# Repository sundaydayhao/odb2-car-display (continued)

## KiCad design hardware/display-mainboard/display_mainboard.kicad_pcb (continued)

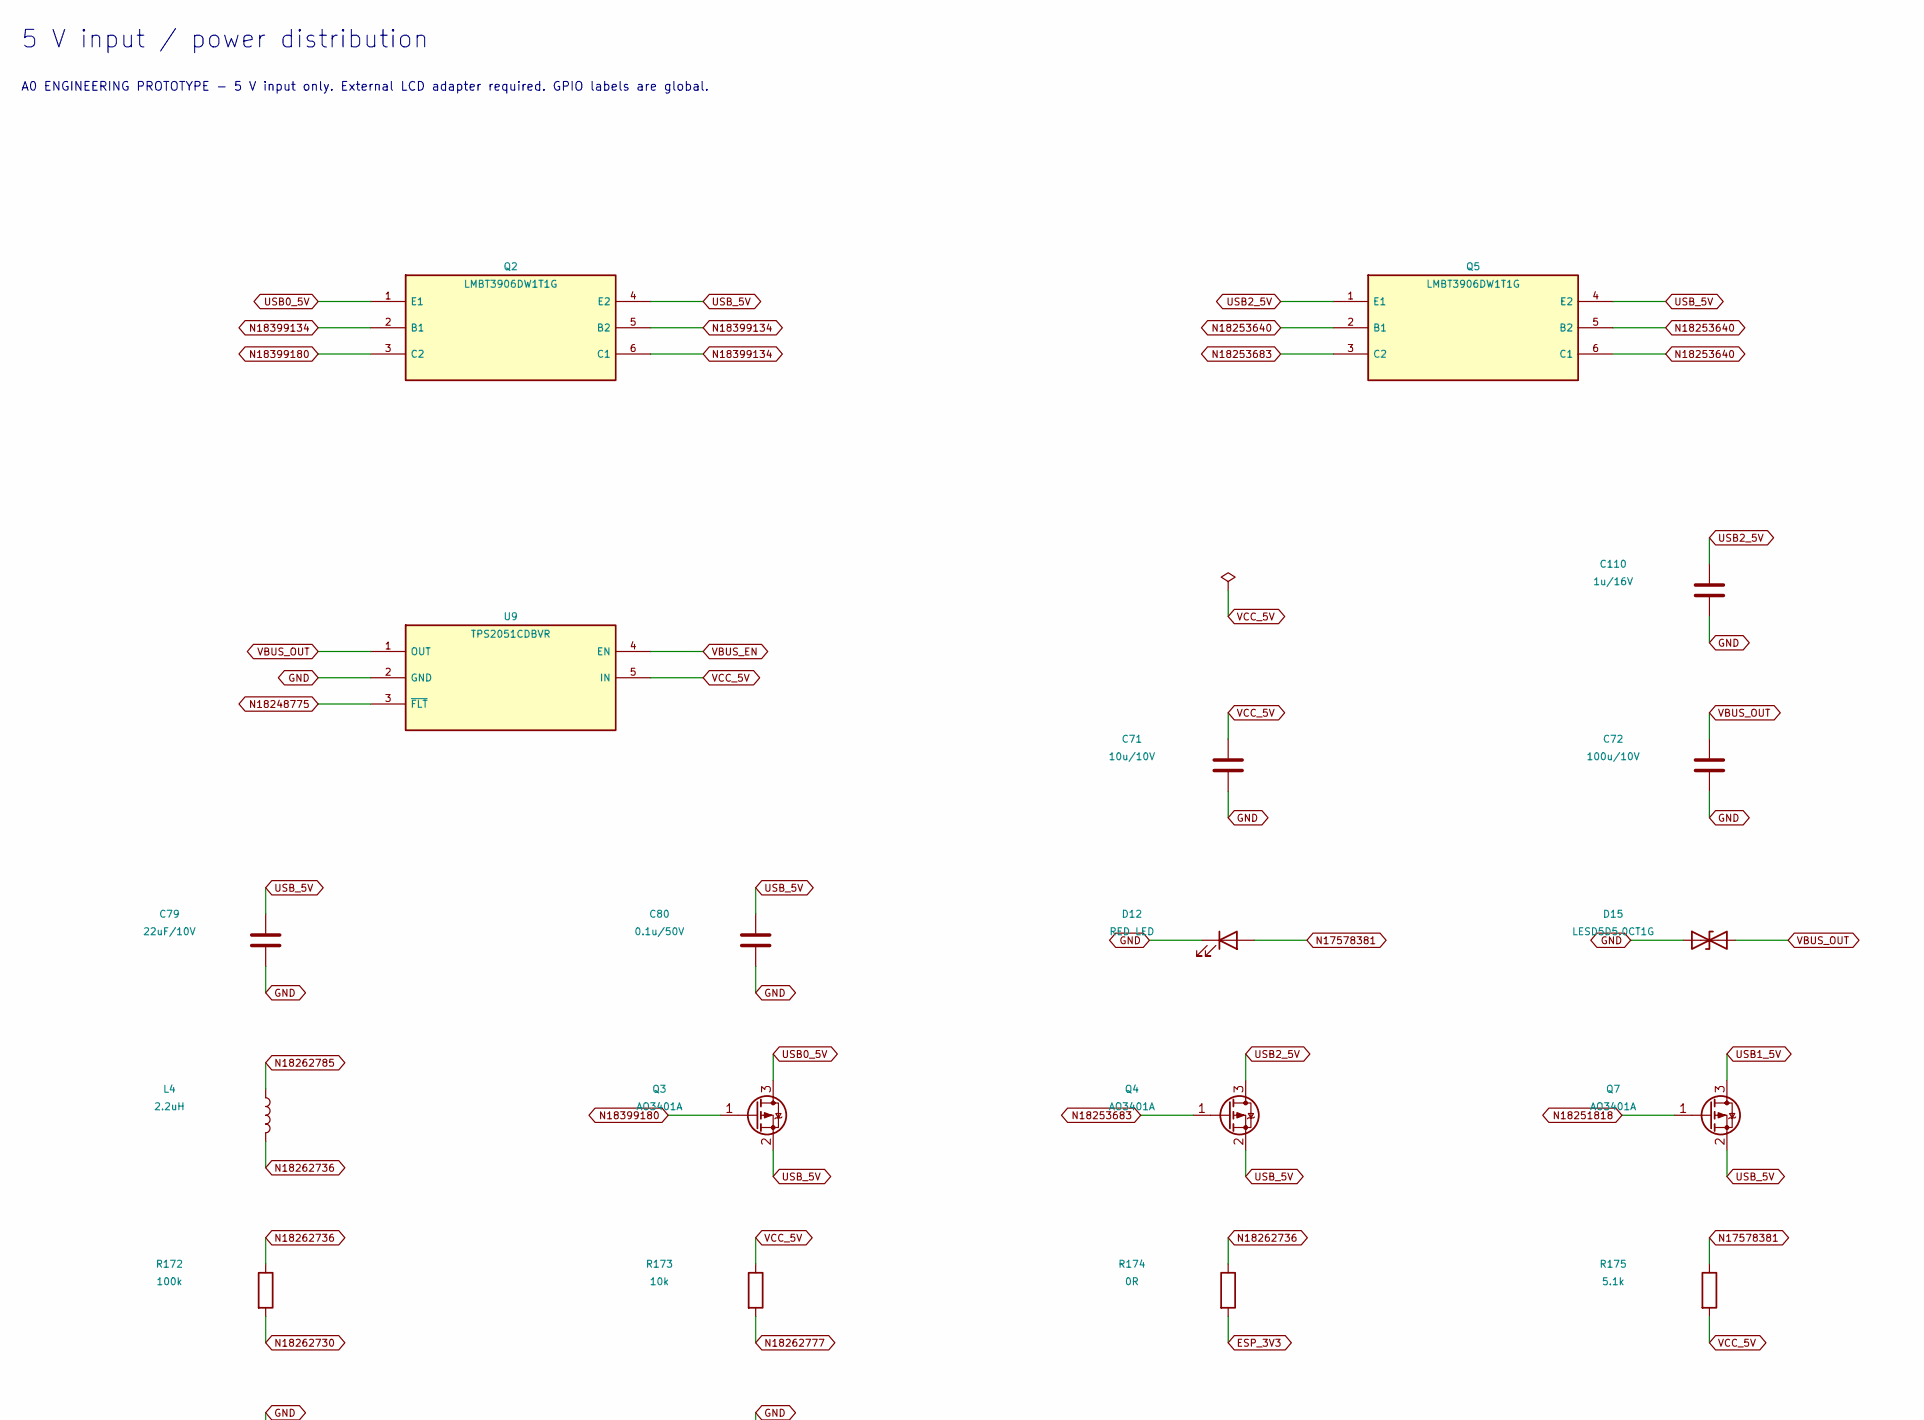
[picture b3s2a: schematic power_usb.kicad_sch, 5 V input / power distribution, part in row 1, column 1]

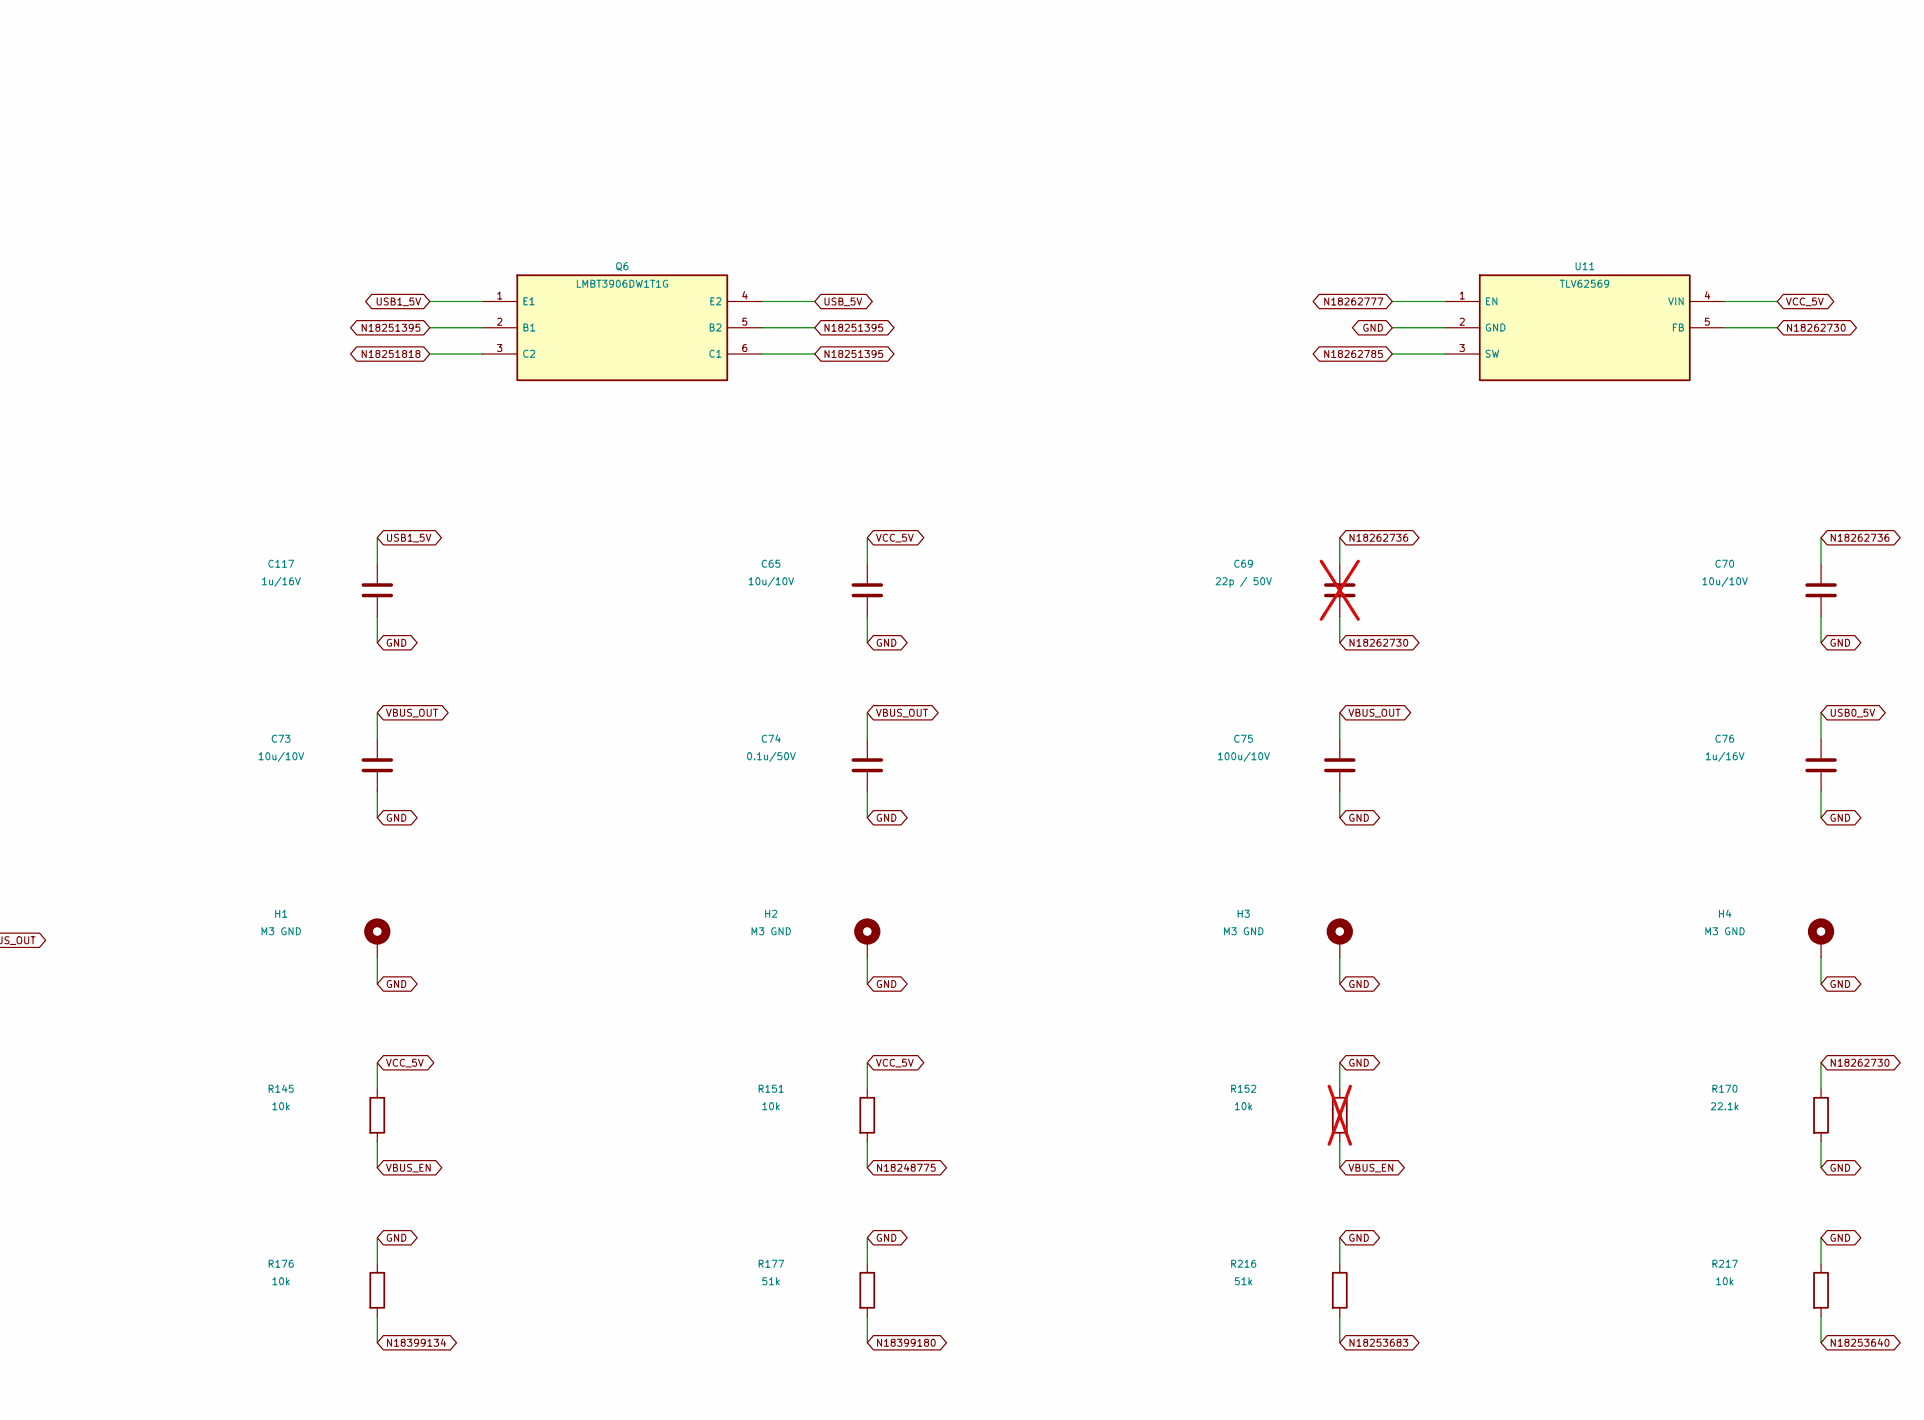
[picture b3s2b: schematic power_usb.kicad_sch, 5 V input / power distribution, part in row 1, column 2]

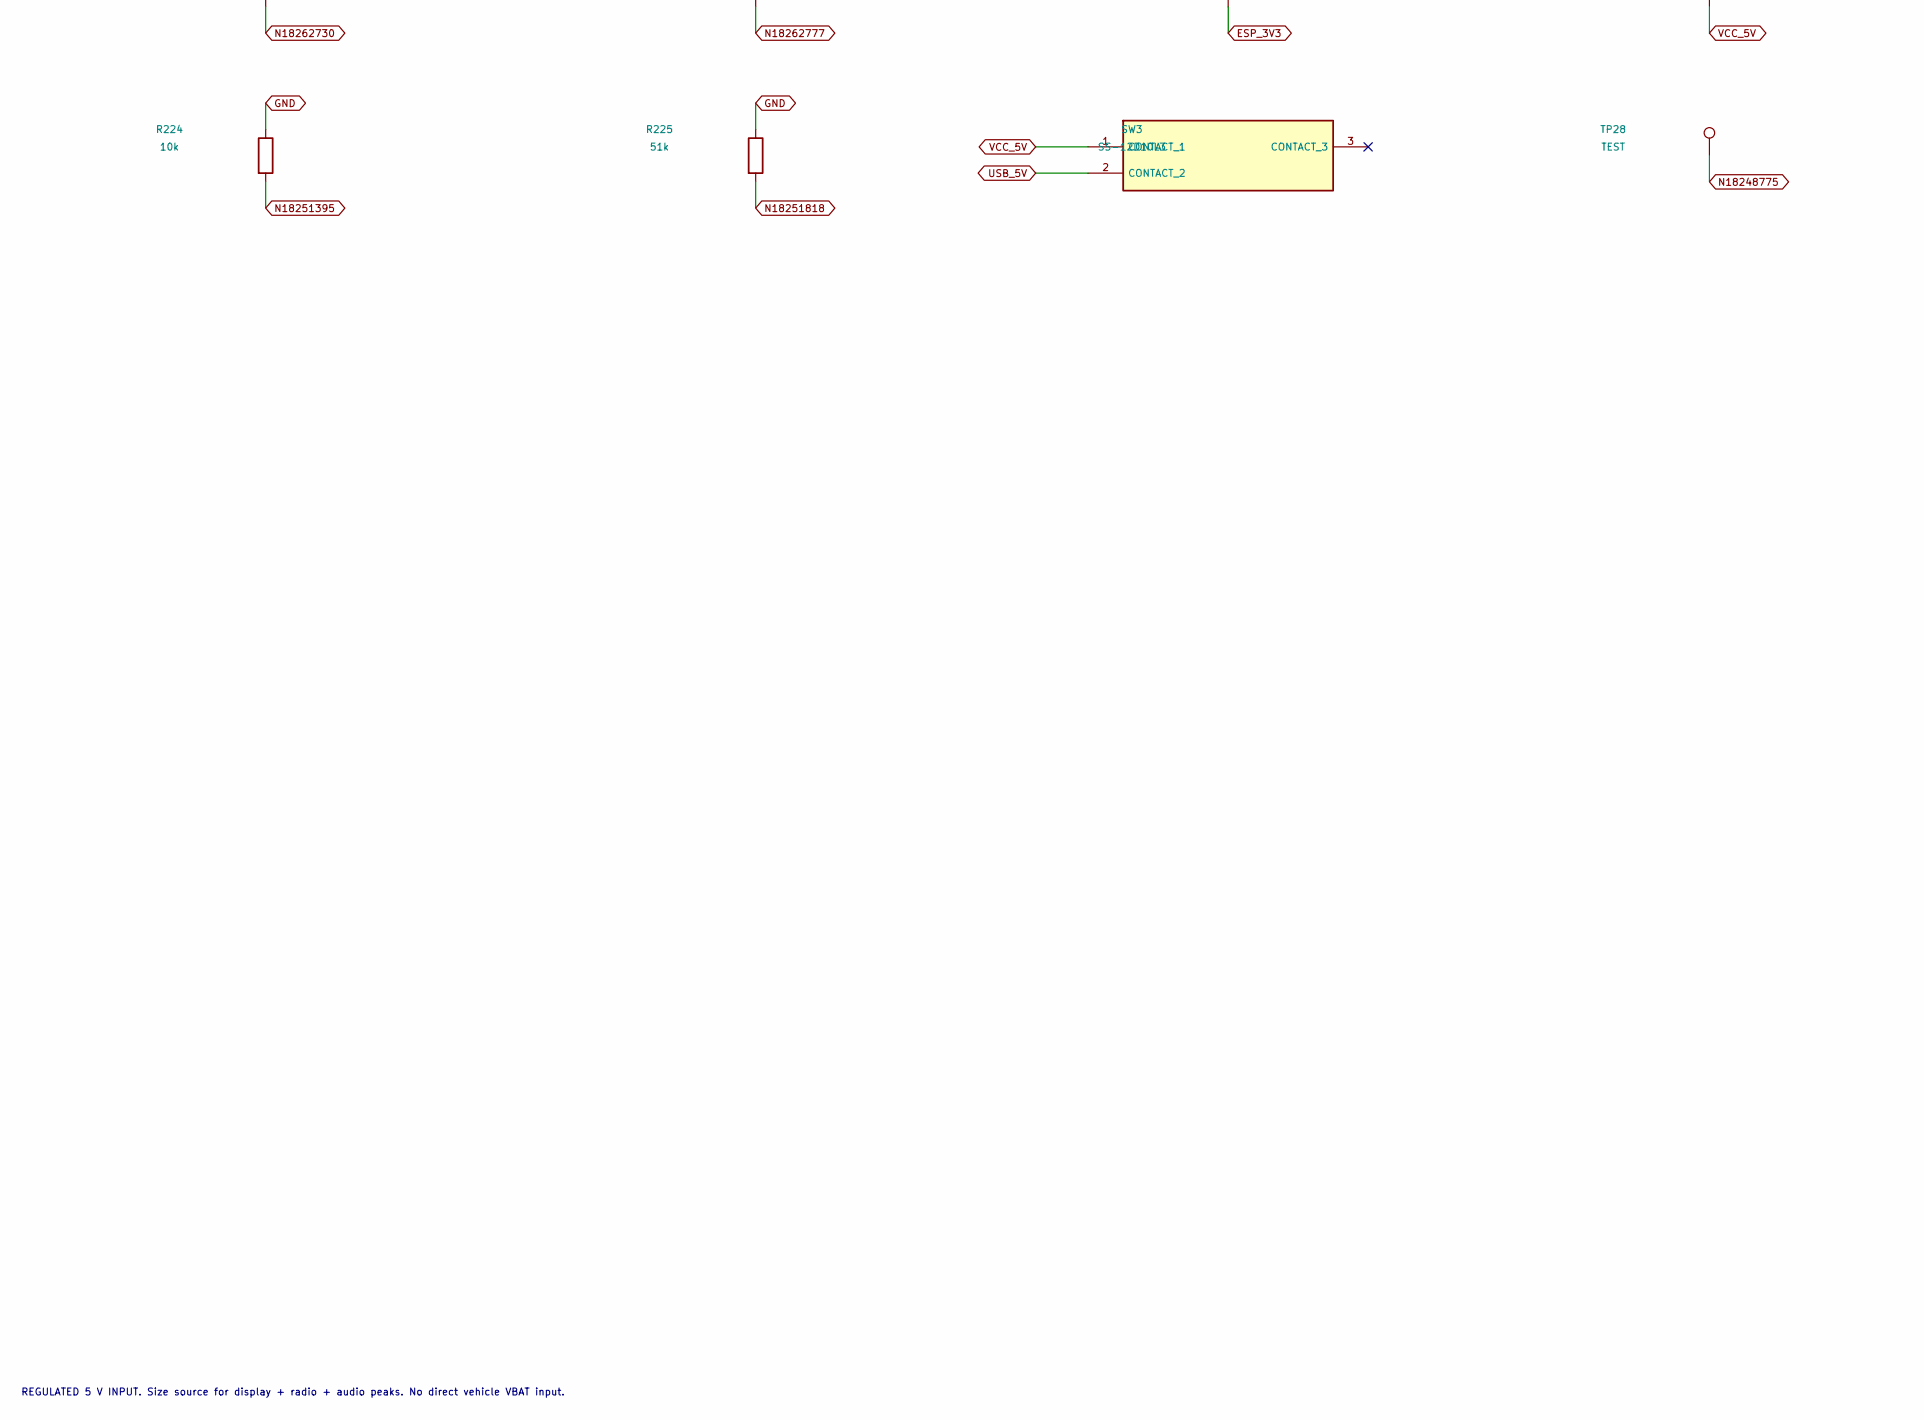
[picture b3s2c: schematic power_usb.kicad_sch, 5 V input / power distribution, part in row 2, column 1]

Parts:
C65, C70, C71, C73: 10u/10V; C0603__ebd4ddd8e4
C69: 22p / 50V; C0402__d1e3d90c7a; not fitted
C72, C75: 100u/10V; C1206__33617ed97b
C74: 0.1u/50V; C0402__d1e3d90c7a
C76, C110, C117: 1u/16V; C0402_097d4b0b__369f5d8838
C79: 22uF/10V; C0603_1ead970f__97efe4e755
C80: 0.1u/50V; C0402_097d4b0b__369f5d8838
D12: RED LED; LED0603__799a6d7898
D15: LESD5D5.0CT1G; SOD523__e205ddb192; MPN LESD5D5.0CT1G
H1, H2, H3, H4: M3 GND; HOLE5_3__7291b2d80b
L4: 2.2uH; L2520__6b96f5deac; MPN WPN252010U2R2MT
Q2, Q5, Q6: LMBT3906DW1T1G; SOT-363__7554680fdb; MPN LMBT3906DW1T1G
Q3, Q4, Q7: AO3401A; SOT23-3__4e657f28a8; MPN AO3401A
R145, R151, R173: 10k; R0402__c67fe31f10
R152: 10k; R0402__c67fe31f10; not fitted
R170: 22.1k; R0402__c67fe31f10
R172: 100k; R0402__c67fe31f10
R174: 0R; R0603__9e2f069e96
R175: 5.1k; R0402__c67fe31f10
R176, R217, R224: 10k; R0402_097d4b0b__cc2a00f46d
R177, R216, R225: 51k; R0402_097d4b0b__cc2a00f46d
SW3: SS-12D10L3; SS-12D10L3__8543e65cef; MPN SS-12D10L3
TP28, TP30: TEST; TPC1__9f0857eafe
U9: TPS2051CDBVR; SOT23-5__cf243f5b81; MPN TPS2051CDBVR
U11: TLV62569; SOT23_0P95_2P6__0905fcd80f; MPN TLV62569DBVR

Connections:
ESP_3V3: R174.2; also elsewhere on the board
N17578381: D12.1 (A), R175.1
N18248775: R151.2, TP28.1, U9.3 (~FLT)
N18251395: Q6.2 (B1), Q6.5 (B2), Q6.6 (C1), R224.2
N18251818: Q6.3 (C2), Q7.1 (G), R225.2
N18253640: Q5.2 (B1), Q5.5 (B2), Q5.6 (C1), R217.2
N18253683: Q4.1 (G), Q5.3 (C2), R216.2
N18262730: C69.2, R170.1, R172.2, U11.5 (FB)
N18262736: C69.1, C70.1, L4.2, R172.1, R174.1, TP30.1
N18262777: R173.2, U11.1 (EN)
N18262785: L4.1, U11.3 (SW)
N18399134: Q2.2 (B1), Q2.5 (B2), Q2.6 (C1), R176.2
N18399180: Q2.3 (C2), Q3.1 (G), R177.2
USB0_5V: C76.1, Q2.1 (E1), Q3.3 (D); also elsewhere on the board
USB2_5V: C110.1, Q4.3 (D), Q5.1 (E1); also elsewhere on the board
USB_5V: C79.1, C80.1, Q2.4 (E2), Q3.2 (S), Q4.2 (S), Q5.4 (E2), Q6.4 (E2), Q7.2 (S), SW3.2 (CONTACT_2)
VBUS_EN: R145.2, R152.2, U9.4 (EN)
VBUS_OUT: C72.1, C73.1, C74.1, C75.1, D15.2 (A2), U9.1 (OUT); also elsewhere on the board
VCC_5V: C65.1, C71.1, R145.1, R151.1, R173.1, R175.2, SW3.1 (CONTACT_1), U9.5 (IN), U11.4 (VIN); also elsewhere on the board

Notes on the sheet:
5 V input / power distribution
A0 ENGINEERING PROTOTYPE - 5 V input only. External LCD adapter required. GPIO labels are global.
REGULATED 5 V INPUT. Size source for display + radio + audio peaks. No direct vehicle VBAT input.
